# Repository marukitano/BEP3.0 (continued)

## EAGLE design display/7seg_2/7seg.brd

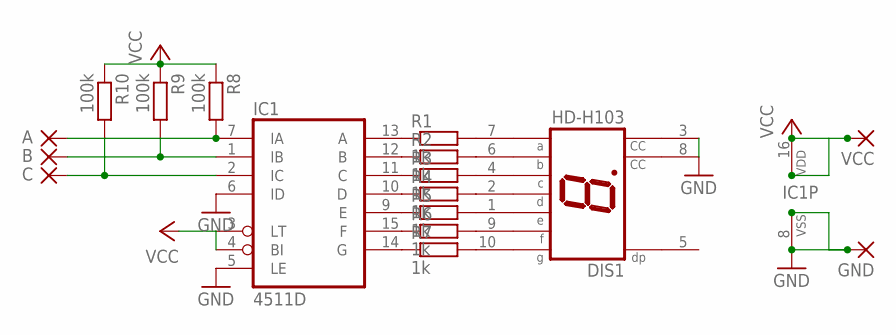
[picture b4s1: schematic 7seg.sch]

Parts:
A: 1,6/0,9
B: 1,6/0,9
C: 1,6/0,9
DIS1: HD-H103; HDSP-M
GND: 1,6/0,9
IC1: 4511D; SO16
R1, R2, R3, R4, R5, R6, R7: 1k; R0805
R8, R9, R10: 100k; R0805
VCC: 1,6/0,9

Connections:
GND: DIS1.3 (CC), DIS1.8 (CC), IC1.5 (LE), IC1.6 (ID), IC1.8 (VSS)
unnamed: IC1.13 (A), R1.1
unnamed: DIS1.7 (A), R1.2
unnamed: IC1.12 (B), R2.1
unnamed: DIS1.6 (B), R2.2
unnamed: IC1.11 (C), R3.1
unnamed: DIS1.4 (C), R3.2
unnamed: IC1.10 (D), R4.1
unnamed: DIS1.2 (D), R4.2
unnamed: IC1.9 (E), R5.1
unnamed: DIS1.1 (E), R5.2
unnamed: IC1.15 (F), R6.1
unnamed: DIS1.9 (F), R6.2
unnamed: IC1.14 (G), R7.1
unnamed: DIS1.10 (G), R7.2
unnamed: A.1, IC1.7 (IA), R8.2
unnamed: B.1, IC1.1 (IB), R9.2
unnamed: C.1, IC1.2 (IC), R10.2
VCC: IC1.3 (LT), IC1.4 (BI), IC1.16 (VDD), R8.1, R9.1, R10.1

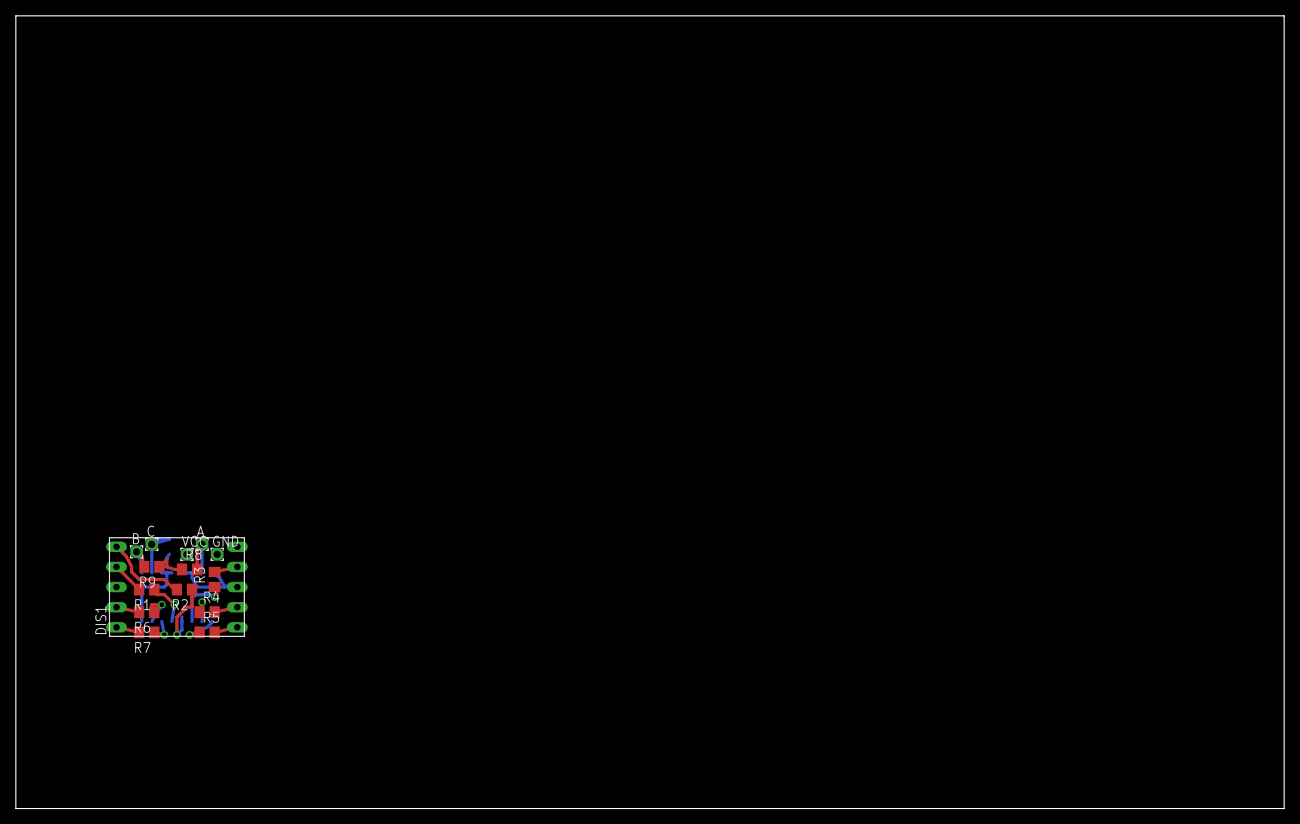
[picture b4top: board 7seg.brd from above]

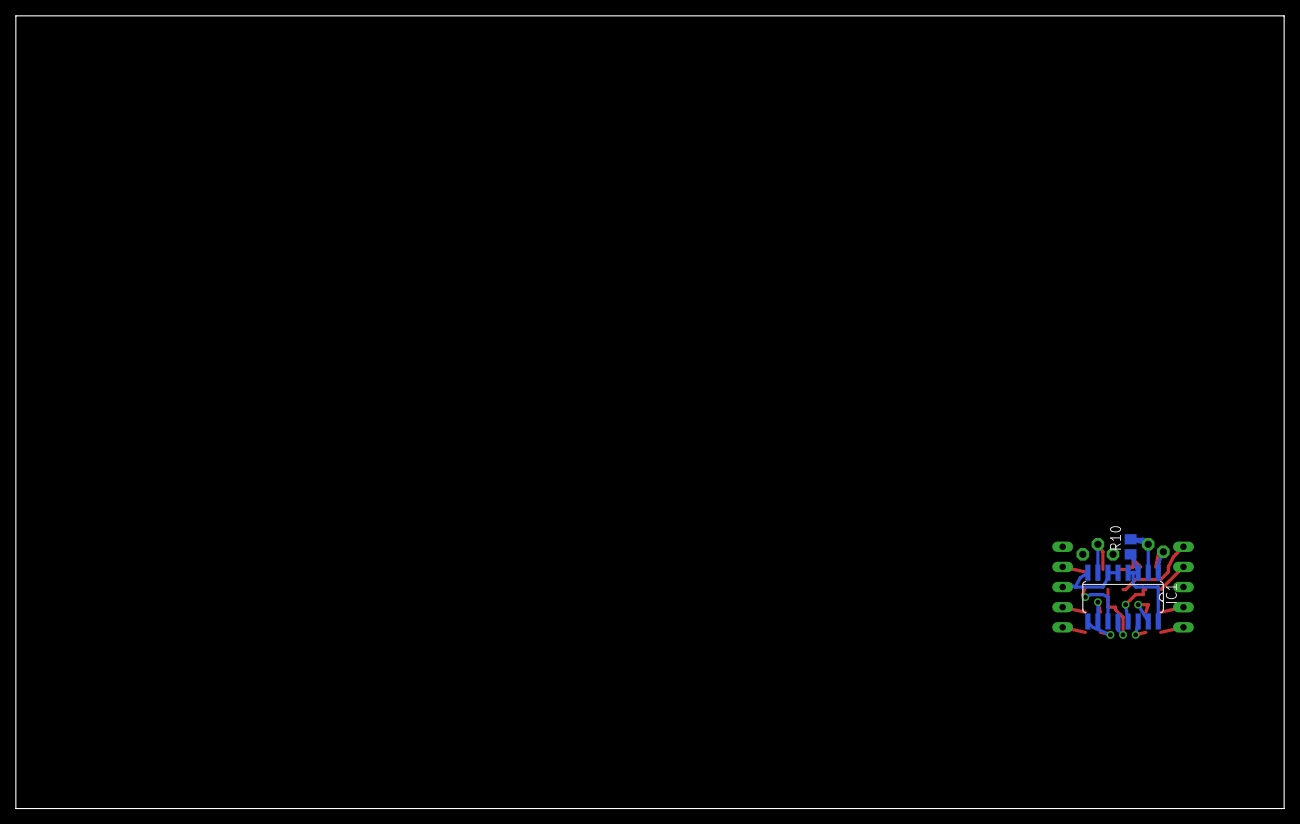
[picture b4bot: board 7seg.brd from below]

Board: 2 copper layers, 160.0 x 100.0 mm, 17 parts (2 on the bottom side), 19 nets.

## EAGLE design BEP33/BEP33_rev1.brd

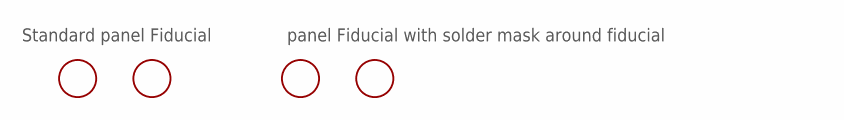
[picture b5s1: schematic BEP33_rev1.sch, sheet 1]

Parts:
FID1, FID2: FIDUCIAL; FIDUCIAL_1MM
FID1B, FID2B: FIDUCIALFIDUCIAL_1MM_WITH_SOLDERMASK; FIDUCIAL_1MM_WITH_SOLDERMASK

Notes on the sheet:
Standard panel Fiducial
panel Fiducial with solder mask around fiducial

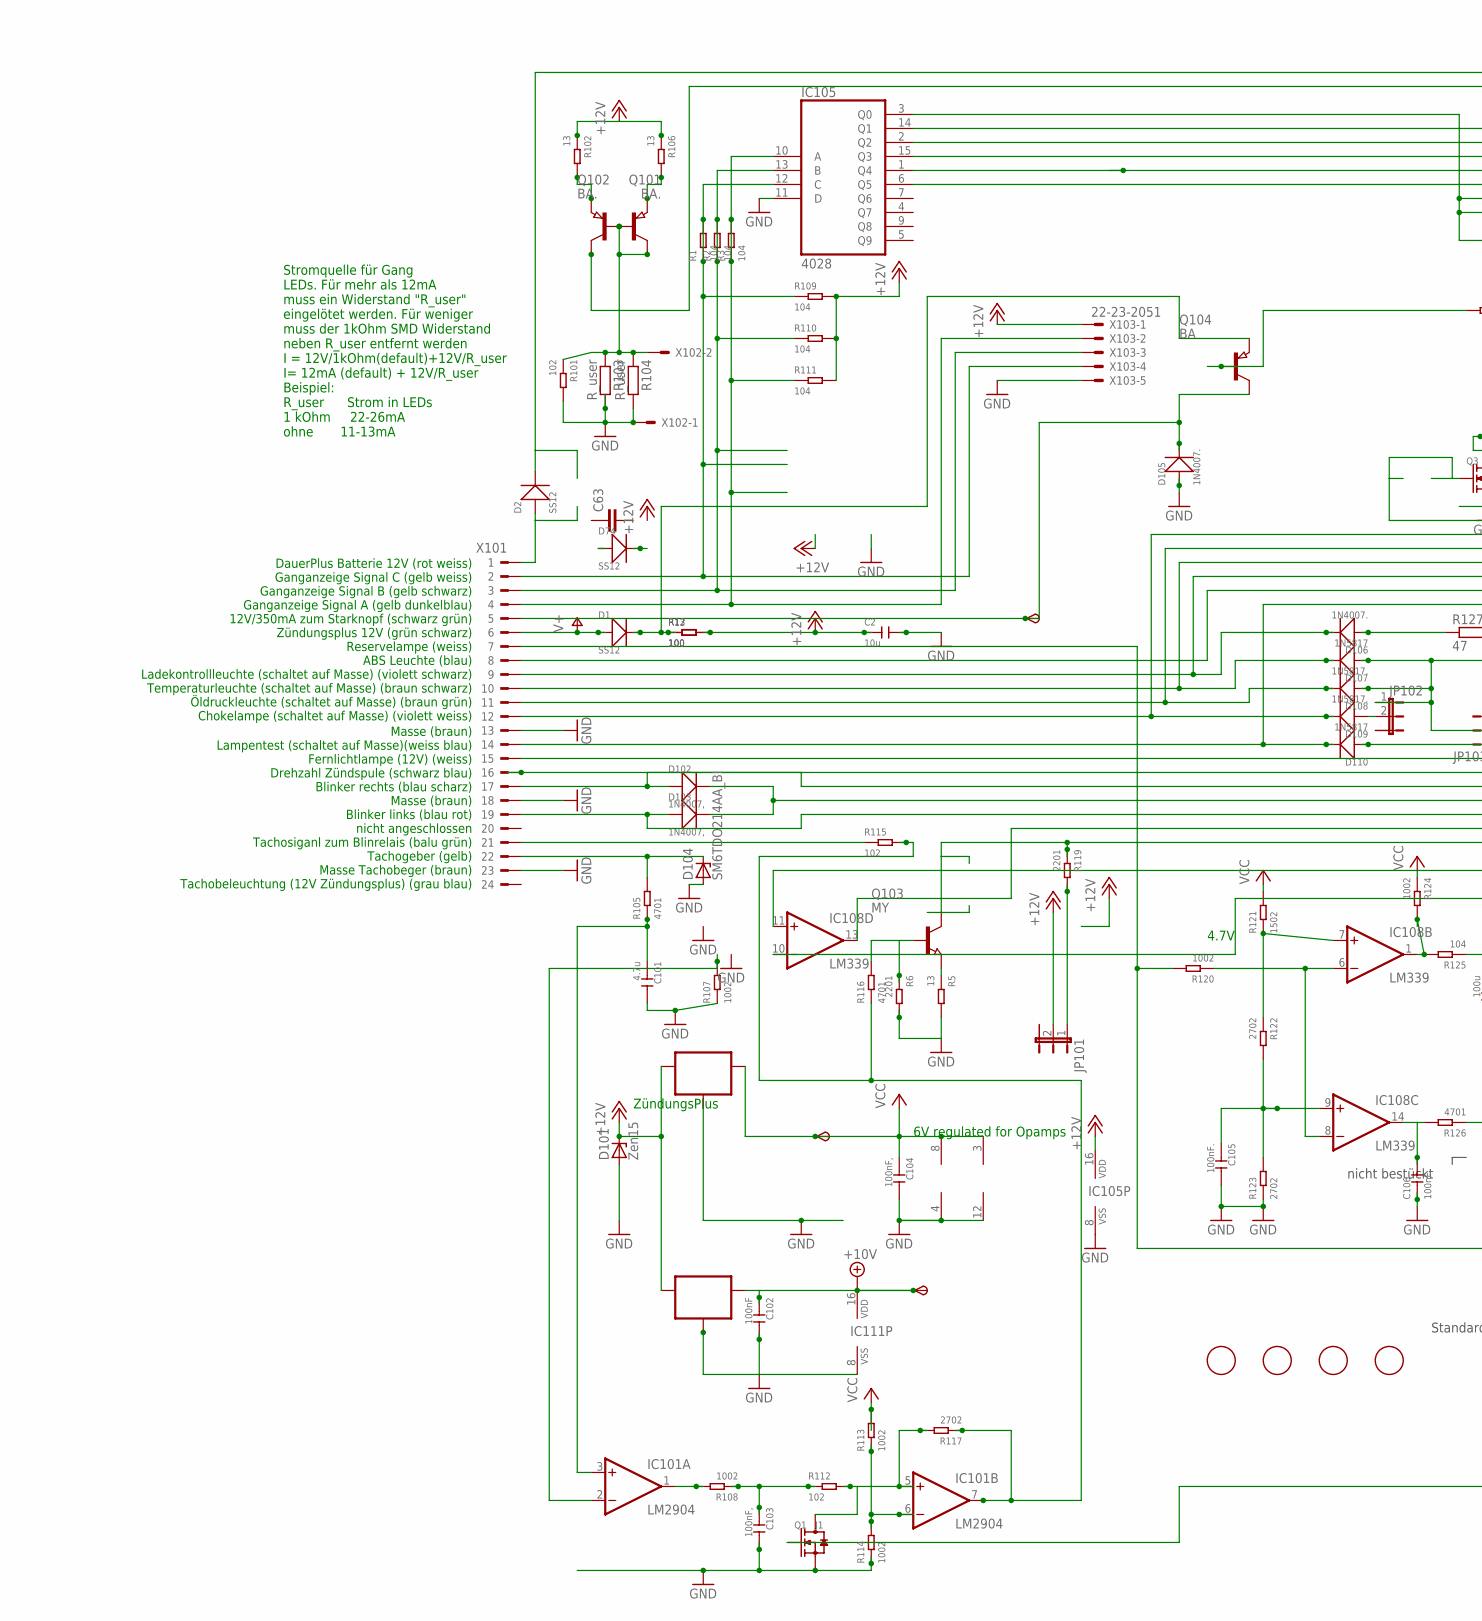
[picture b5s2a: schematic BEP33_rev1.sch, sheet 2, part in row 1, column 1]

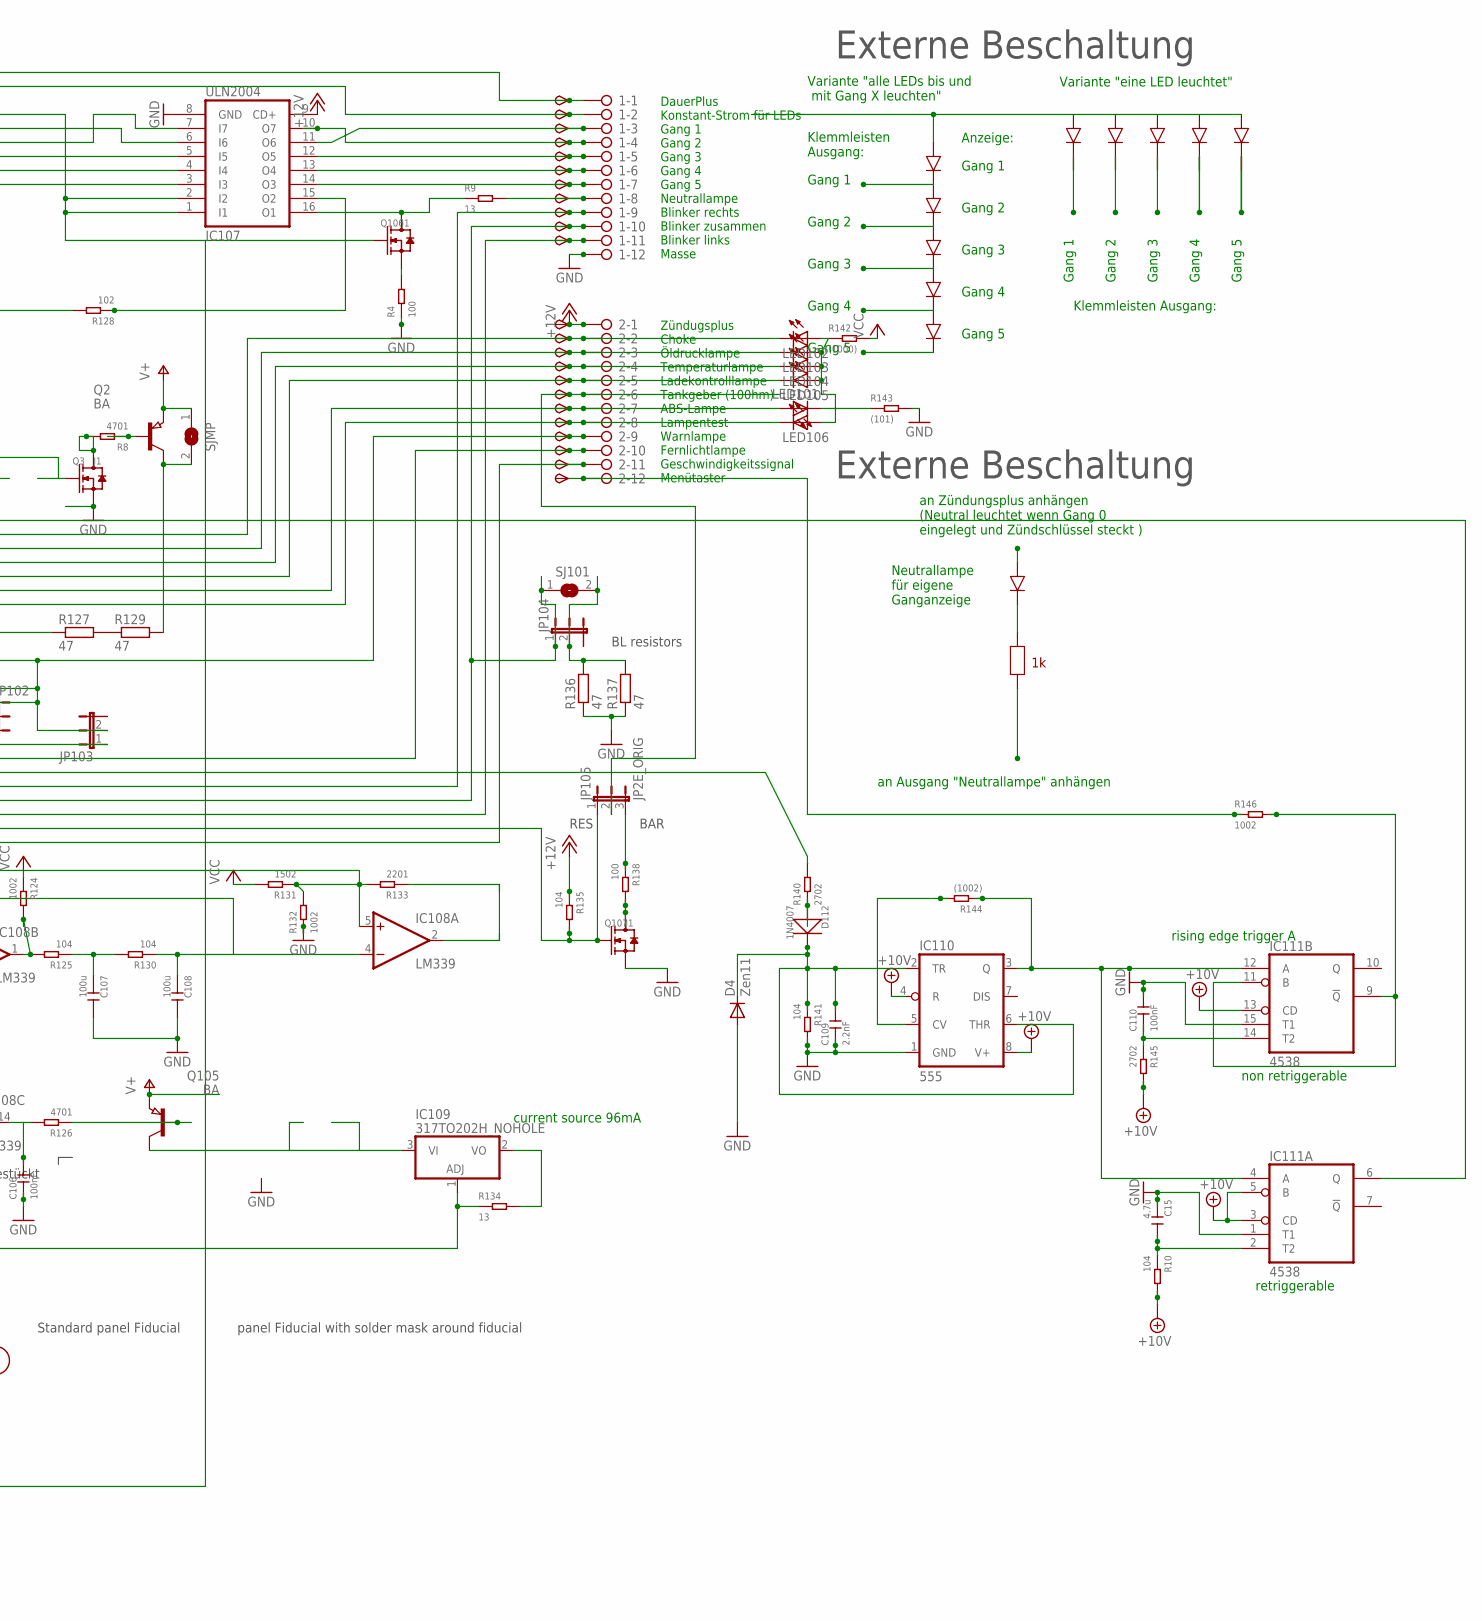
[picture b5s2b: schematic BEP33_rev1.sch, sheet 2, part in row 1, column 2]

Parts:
1, 2: 2081-1132; 12-PIN
6V, 10V: TPSB2.0; B2.0
C2: 10u; C1206
C15, C101: 4.7u; C0805
C63: C-EUC1812K; C1812K
C102, C110: 100nF; C0805
C103, C104: 100nF,; C0805
C105, C106: 100nF.; C0805
C107, C108: 100u; C1206
C109: 2.2nF; C0805
D1, D2, D74: SS12; DO-214AC_SLIM
D4: Zen11; SOD-123_MINI-SMA
D101: Zen15; DO214AA
D102, D103: 1N4007,; DO-214AC
D104: SM6TDO214AA_BI; DO214AA_BI
D105, D106: 1N4007.; DO-214AC
D107, D110: 1N5817; DO-214AC_SLIM
D108, D109: 1N5817.; DO-214AC_SLIM
D112: 1N4007; DO-214AC
FID101, FID102, FID103, FID104: FIDUCIAL; FIDUCIAL_1MM
IC101: LM2904; SO08
IC102: 78L06; SOT89_ROUND
IC104: 78L10; SOT89_ROUND
IC105: 4028; SO16
IC107: ULN2004; SO16
IC108: LM339; SO14
IC109: 317TO202H_NOHOLE; TO220H_NOHOLE
IC110: 555; SO08
IC111: 4538; SO16
JP101, JP102, JP103, JP104: JP2EJP2_SMALLPADS; JP2_SMALLPADS
JP105: JP2E_ORIG; JP2_ORIG_SMALLPADS
LED101, LED102, LED103, LED104, LED105, LED106: LEDLD260; LD260
Q1, Q3, Q106, Q107: J1; SOT-23
Q2, Q104, Q105: BA; SOT89
Q101, Q102: BA.; SOT89
Q103: MY; SOT89
R1, R2, R3, R10, R109, R110, R111, R125, R130, R135, R141: 104; R0805
R4, R12, R13, R138: 100; R0805
R5, R9, R102, R106, R134: 13; R1206
R6, R119, R133: 2201; R0805
R8, R105, R116, R126: 4701; R0805
R101, R112, R115, R128: 102; R0805
R103, R104: R_user; R0805
R107, R108, R113, R114, R120, R124, R132, R146: 1002; R0805
R117, R122, R123, R140, R145: 2702; R0805
R121, R131: 1502; R0805
R127, R129, R136, R137: 47; V235/17_1MM
R142: (1000); R0805
R143: (101); R0805
R144: (1002); R0805
SJ101: SJ
SJMP: SJ
START: TPSB2.0; B2.0
TP1, TP2, TP3, TP4, TP5, TP6, TP7, TP8, TP9, TP10, TP11, TP12, TP13, TP16, TP17, TP18, TP19, TP21, TP22, TP23, TP25, TP26: TPSB2.0; B2.0
TP24: TPSB1,27; B1,27
X101: CON_BMWV2; 24-PIN_V2
X102: 22-23-2021
X103: 22-23-2051

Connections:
+10V: 10V.TP, C102.1, IC104.1 (OUT), IC110.4 (R), IC110.8 (V+), IC111.3 (CD), IC111.5 (B), IC111.13 (CD), IC111.16 (VDD), R10.2, R145.2; also elsewhere on the board
+12V: 2.1, C2.1, D101.C, IC102.3 (IN), IC104.3 (IN), IC105.16 (VDD), IC107.9 (CD+), JP101.2, R12.2, R13.2, R102.1, R106.1, R109.2, R110.2, R111.2, R135.1, TP12.TP, X103.1; also elsewhere on the board
+12V1: 2.11, Q103.2 (C), R119.1, TP26.TP
GND: 1.12, C2.2, C15.1, C101.2, C102.2, C103.2, C104.2, C105.2, C106.1, C107.2, C108.2, C109.1, C110.2, D4.A, D101.A, D104.A, D105.1 (+), IC101.4 (V-), IC102.2 (GND), IC102.2@1 (GND), IC104.2 (GND), IC104.2@1 (GND), IC105.8 (VSS), IC105.11 (D), IC107.8 (GND), IC108.12 (GND), IC110.1 (GND), IC111.1 (T1), IC111.8 (VSS), IC111.15 (T1), Q1.2 (S), Q3.2 (S), Q107.2 (S), R4.1, R5.2, R6.2, R101.2, R103.2, R104.2, R107.1, R114.1, R123.1, R132.1, R136.1, R137.1, R141.2, R143.2, X101.13, X101.18, X101.23, X102.1, X103.5; also elsewhere on the board
unnamed: 2.9, D107.1 (+), D108.1 (+), JP102.1, JP103.2, TP24.TP
unnamed: IC105.10 (A), R3.1, R3.2, R111.1, X101.4, X103.2
unnamed: IC105.13 (B), R2.1, R2.2, R110.1, X101.3, X103.3
unnamed: 2.7, LED101.A, TP22.TP, X101.8
unnamed: Q101.3 (E), R102.2
unnamed: Q2.1 (B), R8.1
unnamed: IC101.2 (-IN), R107.2
unnamed: R127.2, R129.1
unnamed: Q102.3 (E), R106.2
unnamed: D105.2 (-), Q104.2 (C), START.TP, X101.5
unnamed: 2.2, D109.2 (-), LED102.K (C), TP16.TP, X101.12
unnamed: 2.3, D108.2 (-), LED103.K (C), TP17.TP, X101.11
unnamed: 2.4, D107.2 (-), LED104.K (C), TP18.TP, X101.10
unnamed: IC109.3 (VI), Q105.2 (C)
unnamed: IC108.6 (-IN), IC108.8 (-IN), R120.1
unnamed: IC105.12 (C), R1.1, R1.2, R109.1, X101.2, X103.4
unnamed: IC105.15 (Q3), IC107.5 (I5)
unnamed: 2.8, D110.2 (-), LED106.K (C), TP23.TP, X101.14
unnamed: 1.9, D102.1 (+), TP9.TP, X101.17
unnamed: 1.11, D103.1 (+), TP11.TP, X101.19
unnamed: IC111.9 (!Q), IC111.11 (B), R146.2
unnamed: D104.C, R105.2, X101.22
unnamed: C101.1, IC101.3 (+IN), R105.1
unnamed: 1.6, IC107.13 (O4), TP6.TP
unnamed: 1.7, IC107.14 (O3), TP7.TP
unnamed: D1.2 (-), Q104.3 (E), R12.1, R13.1
unnamed: 2.6, JP105.2, TP21.TP
unnamed: JP101.1, R119.2
unnamed: C105.1, IC108.9 (+IN), R122.2, R123.2
unnamed: C106.2, IC108.14 (OUT), R126.2
unnamed: Q3.3 (D), R8.2
unnamed: LED101.K (C), R143.1
unnamed: IC109.1 (ADJ), R120.2, R134.1, X101.7
unnamed: Q105.1 (B), R126.1
unnamed: IC105.2 (Q2), IC107.7 (I7)
unnamed: 1.3, IC107.11 (O6), TP3.TP
unnamed: 1.5, IC107.12 (O5), TP5.TP
unnamed: LED102.A, LED103.A, LED104.A, LED105.A, LED106.A, R142.1
unnamed: R140.2, X101.16
unnamed: Q104.1 (B), R128.2
unnamed: IC105.3 (Q0), IC107.1 (I1), IC107.2 (I2), Q1.1 (G), Q106.1 (G)
unnamed: C107.1, R125.1, R130.2
unnamed: C108.1, IC108.4 (-IN), IC108.10 (-IN), R130.1
unnamed: IC108.5 (+IN), IC108.11 (+IN), R131.1, R132.2, R133.2
unnamed: Q107.3 (D), R138.2
unnamed: IC111.6 (Q), Q3.1 (G)
unnamed: IC105.1 (Q4), IC107.4 (I4)
unnamed: R115.1, X101.21
unnamed: IC107.16 (O1), Q106.3 (D), R9.1
unnamed: 2.10, TP25.TP, X101.15
unnamed: D106.1 (+), R127.1
unnamed: 2.5, D106.2 (-), LED105.K (C), TP19.TP, X101.9
unnamed: IC105.14 (Q1), IC107.6 (I6)
unnamed: Q101.1 (B), Q102.1 (B), Q102.2 (C), R101.1, R103.1, R104.1, X102.2
unnamed: 1.8, R9.2, TP8.TP
unnamed: 1.2, Q101.2 (C), TP2.TP
unnamed: IC108.13 (OUT), JP105.1, Q107.1 (G), R135.2
unnamed: IC105.6 (Q5), IC107.3 (I3)
unnamed: IC109.2 (VO), R134.2
unnamed: IC110.5 (CV), R144.2
unnamed: 1.4, IC107.10 (O7), TP4.TP
unnamed: 1.1, D2.2 (-), TP1.TP
unnamed: IC108.7 (+IN), R121.1, R122.1
unnamed: Q106.2 (S), R4.2
unnamed: Q103.1 (B), R6.1, R116.2
unnamed: IC110.3 (Q), IC111.4 (A), IC111.12 (A), R144.1
unnamed: D112.1 (+), R140.1
unnamed: IC107.15 (O2), R128.1
unnamed: C110.1, IC111.14 (T2), R145.1
unnamed: 2.12, R146.1, TP13.TP
unnamed: D2.1 (+), X101.1
unnamed: IC101.1 (OUT), R108.2
unnamed: 1.10, D102.2 (-), D103.2 (-), JP104.1, SJ101.1, TP10.TP
unnamed: JP104.2, R136.2, R137.2, SJ101.2
unnamed: D109.1 (+), JP102.2
unnamed: C103.1, R108.1, R112.1
unnamed: IC101.5 (+IN), Q1.3 (D), R112.2, R117.2
unnamed: D110.1 (+), JP103.1
unnamed: JP105.3, R138.1
unnamed: Q103.3 (E), R5.1
unnamed: IC101.6 (-IN), R113.1, R114.2
unnamed: C109.2, D4.C, D112.2 (-), IC110.2 (TR), IC110.6 (THR), R141.1
unnamed: C15.2, IC111.2 (T2), R10.1
unnamed: Q2.2 (C), R129.2, SJMP.2
unnamed: IC101.7 (OUT), R115.2, R116.1, R117.1
unnamed: IC108.2 (OUT), R133.1
unnamed: IC108.1 (OUT), R124.2, R125.2
V+: D1.1 (+), Q2.3 (E), Q105.3 (E), SJMP.1, X101.6; also elsewhere on the board
VCC: 6V.TP, C104.1, IC101.8 (V+), IC102.1 (OUT), IC108.3 (V+), R113.2, R121.2, R124.1, R131.2, R142.2; also elsewhere on the board

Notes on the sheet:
6V regulated for Opamps
current source 96mA
ZündungsPlus
Zündugsplus Choke Öldrucklampe Temperaturlampe Ladekontrolllampe Tankgeber (100hm) ABS-Lampe Lampentest Warnlampe Fernlichtlampe Geschwindigkeitssignal Menütaster
DauerPlus Konstant-Strom für LEDs Gang 1 Gang 2 Gang 3 Gang 4 Gang 5 Neutrallampe Blinker rechts Blinker zusammen Blinker links Masse
DauerPlus Batterie 12V (rot weiss) Ganganzeige Signal C (gelb weiss) Ganganzeige Signal B (gelb schwarz) Ganganzeige Signal A (gelb dunkelblau) 12V/350mA zum Starknopf (schwarz grün) Zündungsplus 12V (grün schwarz) Reservelampe (weiss) ABS Leuchte (blau) Ladekontrollleuchte (schaltet auf Masse) (vi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
Masse (braun) Lampentest (schaltet auf Masse)(weiss blau) Fernlichtlampe (12V) (weiss) Drehzahl Zündspule (schwarz blau) Blinker rechts (blau scharz) Masse (braun) Blinker links (blau rot) nicht angeschlossen Tachosiganl zum Blinrelais (balu grün) Tachogeber (gelb) Masse Tachobeger (braun) Tachobel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
4.7V
Stromquelle für Gang LEDs. Für mehr als 12mA muss ein Widerstand "R_user" eingelötet werden. Für weniger muss der 1kOhm SMD Widerstand neben R_user entfernt werden I = 12V/1kOhm(default)+12V/R_user I= 12mA (default) + 12V/R_user Beispiel: R_user Strom in LEDs 1 kOhm 22-26mA ohne 11-13mA
Gang 1
Gang 2
Gang 3
Gang 4
Gang 5
Variante "eine LED leuchtet"
Variante "alle LEDs bis und mit Gang X leuchten"
Klemmleisten Ausgang:
Klemmleisten Ausgang:
an Zündungsplus anhängen (Neutral leuchtet wenn Gang 0 eingelegt und Zündschlüssel steckt )
an Ausgang "Neutrallampe" anhängen
Neutrallampe für eigene Ganganzeige
Externe Beschaltung
Anzeige:
nicht bestückt
rising edge trigger A
BAR
RES
BL resistors
Standard panel Fiducial
panel Fiducial with solder mask around fiducial
non retriggerable
retriggerable

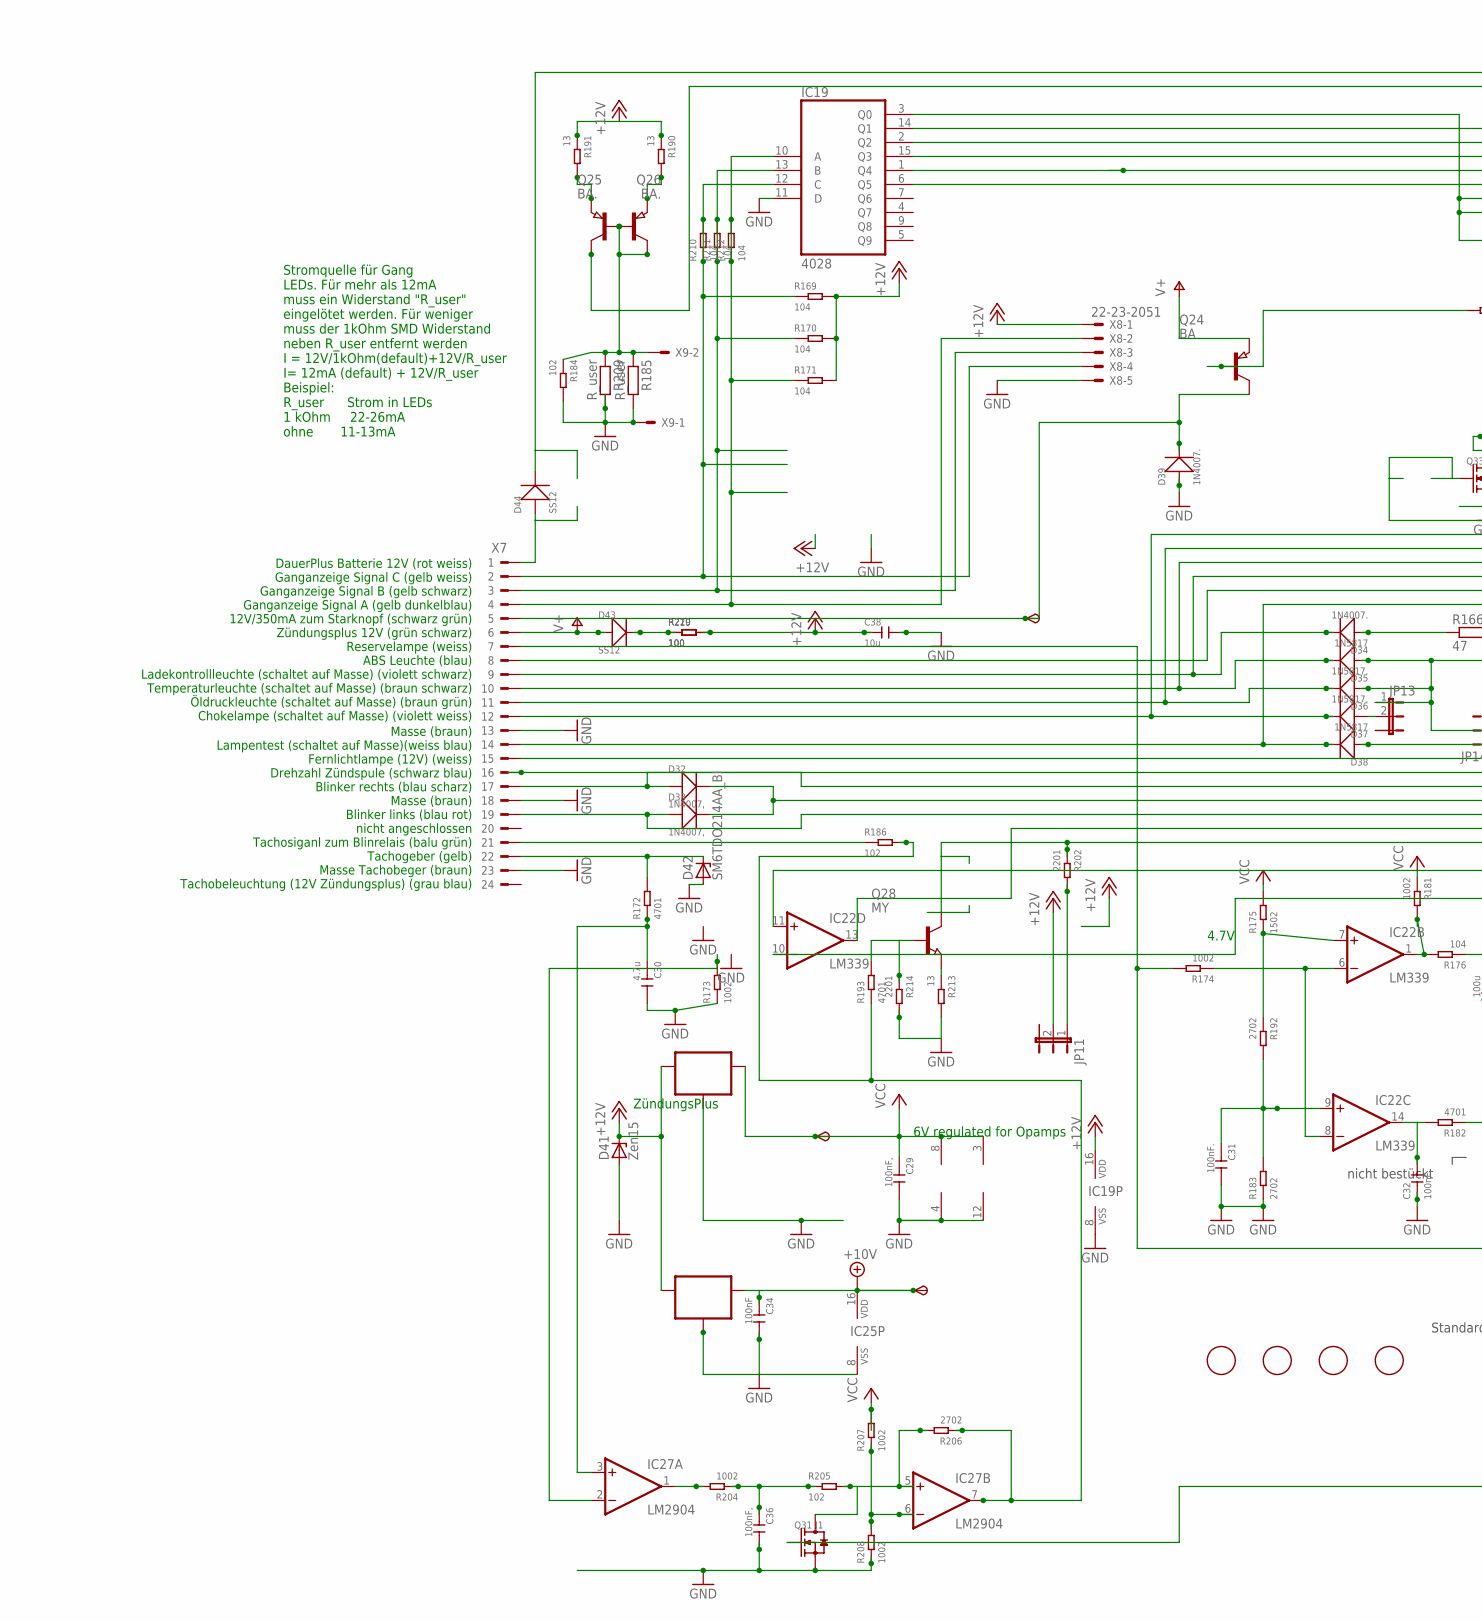
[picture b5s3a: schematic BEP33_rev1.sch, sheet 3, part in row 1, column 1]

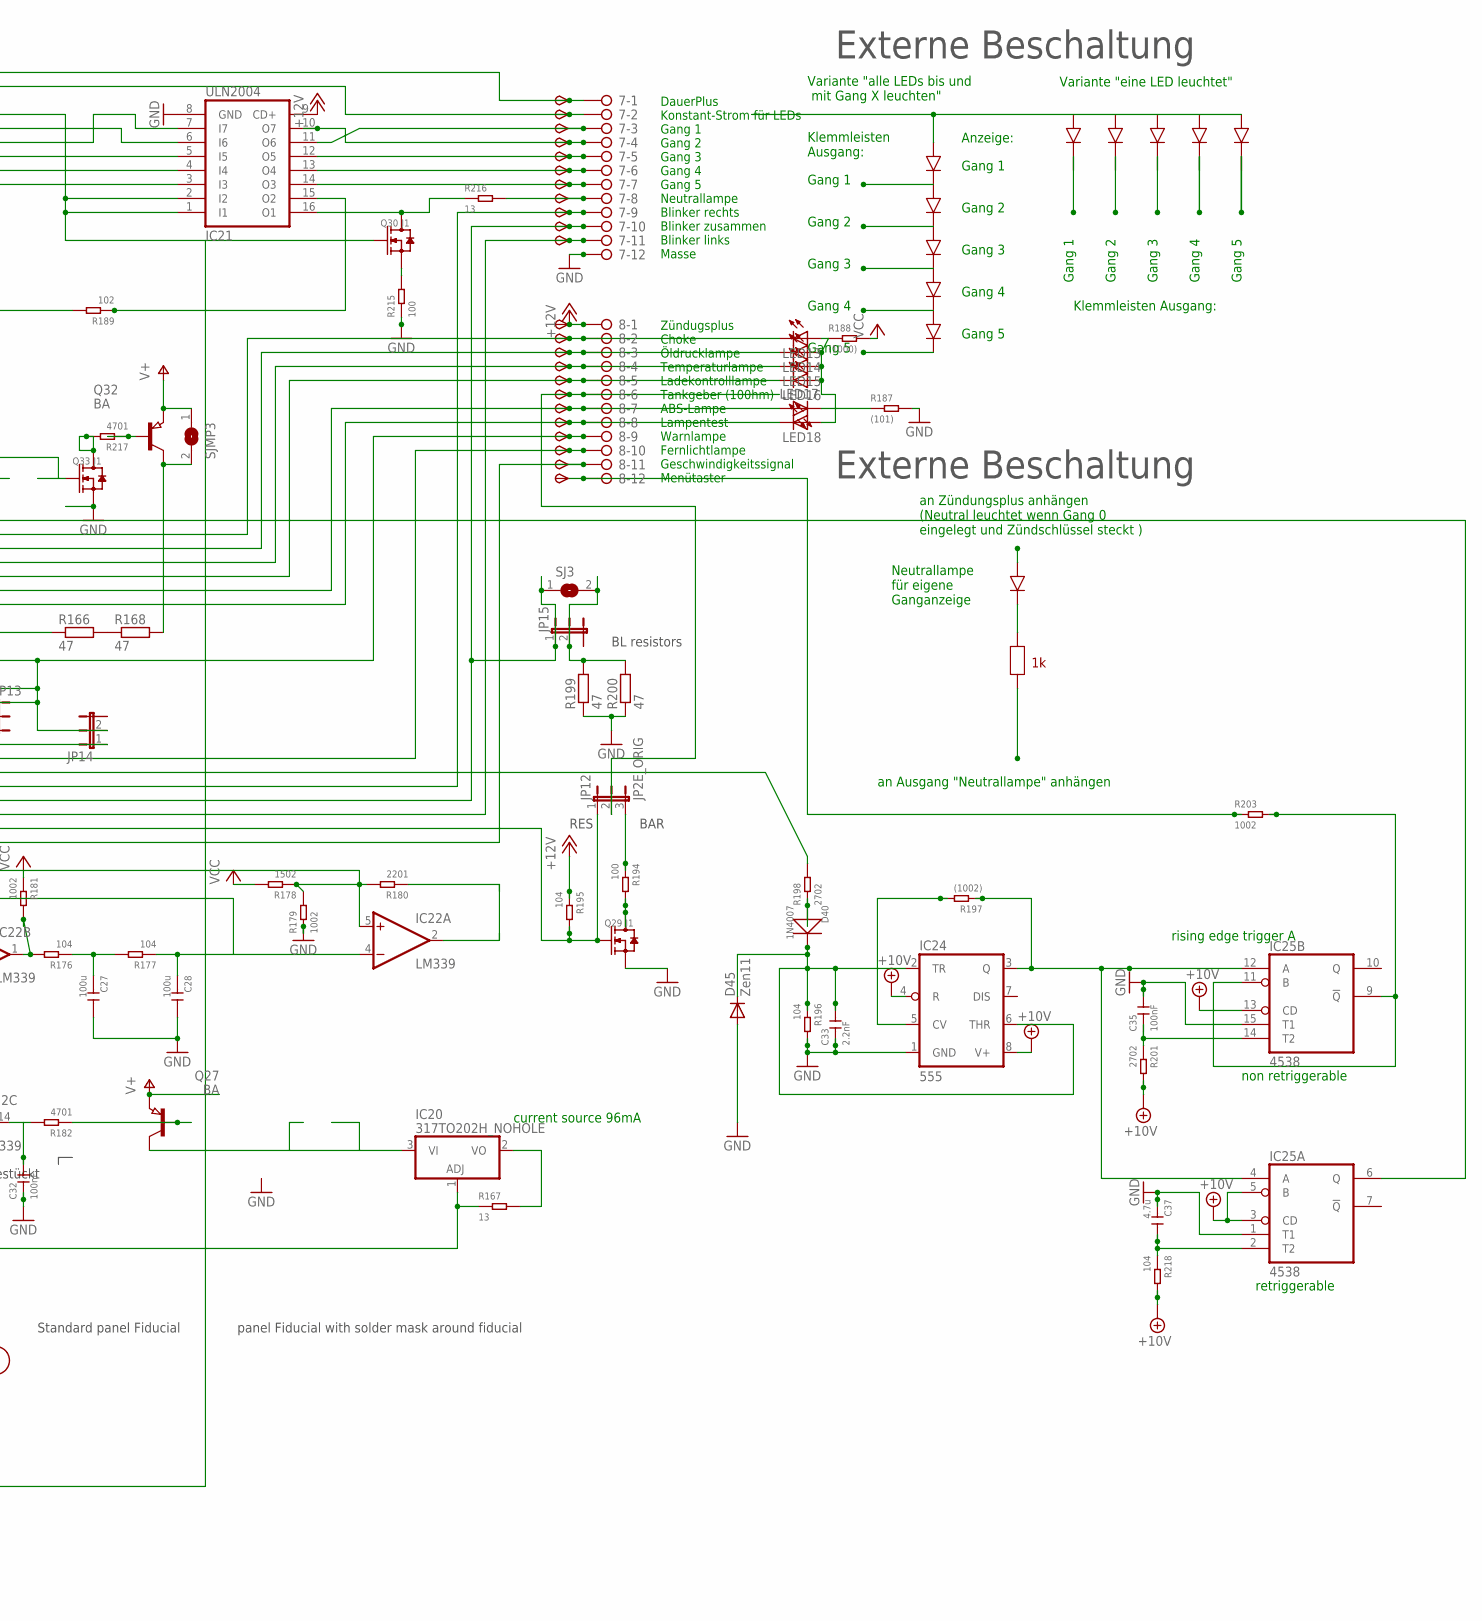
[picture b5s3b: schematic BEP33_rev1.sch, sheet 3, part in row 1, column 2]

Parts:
6V3, 10V3: TPSB2.0; B2.0
7, 8: 2081-1132; 12-PIN
C27, C28: 100u; C1206
C29, C36: 100nF,; C0805
C30, C37: 4.7u; C0805
C31, C32: 100nF.; C0805
C33: 2.2nF; C0805
C34, C35: 100nF; C0805
C38: 10u; C1206
D32, D33: 1N4007,; DO-214AC
D34, D39: 1N4007.; DO-214AC
D35, D38: 1N5817; DO-214AC_SLIM
D36, D37: 1N5817.; DO-214AC_SLIM
D40: 1N4007; DO-214AC
D41: Zen15; DO214AA
D42: SM6TDO214AA_BI; DO214AA_BI
D43, D44: SS12; DO-214AC_SLIM
D45: Zen11; SOD-123_MINI-SMA
FID11, FID12, FID13, FID14: FIDUCIAL; FIDUCIAL_1MM
IC19: 4028; SO16
IC20: 317TO202H_NOHOLE; TO220H_NOHOLE
IC21: ULN2004; SO16
IC22: LM339; SO14
IC23: 78L06; SOT89_ROUND
IC24: 555; SO08
IC25: 4538; SO16
IC26: 78L10; SOT89_ROUND
IC27: LM2904; SO08
JP11, JP13, JP14, JP15: JP2EJP2_SMALLPADS; JP2_SMALLPADS
JP12: JP2E_ORIG; JP2_ORIG_SMALLPADS
LED13, LED14, LED15, LED16, LED17, LED18: LEDLD260; LD260
Q24, Q27, Q32: BA; SOT89
Q25, Q26: BA.; SOT89
Q28: MY; SOT89
Q29, Q30, Q31, Q33: J1; SOT-23
R166, R168, R199, R200: 47; V235/17_1MM
R167, R190, R191, R213, R216: 13; R1206
R169, R170, R171, R176, R177, R195, R196, R210, R211, R212, R218: 104; R0805
R172, R182, R193, R217: 4701; R0805
R173, R174, R179, R181, R203, R204, R207, R208: 1002; R0805
R175, R178: 1502; R0805
R180, R202, R214: 2201; R0805
R183, R192, R198, R201, R206: 2702; R0805
R184, R186, R189, R205: 102; R0805
R185, R209: R_user; R0805
R187: (101); R0805
R188: (1000); R0805
R194, R215, R219, R220: 100; R0805
R197: (1002); R0805
SJ3: SJ
SJMP3: SJ
START3: TPSB2.0; B2.0
TP70, TP71, TP72, TP73, TP74, TP75, TP76, TP77, TP78, TP79, TP80, TP81, TP82, TP83, TP84, TP85, TP86, TP87, TP89, TP90, TP91, TP92: TPSB2.0; B2.0
TP88: TPSB1,27; B1,27
X7: CON_BMWV2; 24-PIN_V2
X8: 22-23-2051
X9: 22-23-2021

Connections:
+10V: 10V3.TP, C34.1, IC24.4 (R), IC24.8 (V+), IC25.3 (CD), IC25.5 (B), IC25.13 (CD), IC25.16 (VDD), IC26.1 (OUT), R201.2, R218.2; also elsewhere on the board
+12V: 8.1, C38.1, D41.C, IC19.16 (VDD), IC21.9 (CD+), IC23.3 (IN), IC26.3 (IN), JP11.2, R169.2, R170.2, R171.2, R190.1, R191.1, R195.1, R219.2, R220.2, TP91.TP, X8.1; also elsewhere on the board
+12V4: 8.11, Q28.2 (C), R202.1, TP90.TP
GND: 7.12, C27.2, C28.2, C29.2, C30.2, C31.2, C32.1, C33.1, C34.2, C35.2, C36.2, C37.1, C38.2, D39.1 (+), D41.A, D42.A, D45.A, IC19.8 (VSS), IC19.11 (D), IC21.8 (GND), IC22.12 (GND), IC23.2 (GND), IC23.2@1 (GND), IC24.1 (GND), IC25.1 (T1), IC25.8 (VSS), IC25.15 (T1), IC26.2 (GND), IC26.2@1 (GND), IC27.4 (V-), Q29.2 (S), Q31.2 (S), Q33.2 (S), R173.1, R179.1, R183.1, R184.2, R185.2, R187.2, R196.2, R199.1, R200.1, R208.1, R209.2, R213.2, R214.2, R215.1, X7.13, X7.18, X7.23, X8.5, X9.1; also elsewhere on the board
unnamed: R166.2, R168.1
unnamed: 8.9, D35.1 (+), D36.1 (+), JP13.1, JP14.2, TP88.TP
unnamed: IC19.10 (A), R171.1, R212.1, R212.2, X7.4, X8.2
unnamed: IC19.13 (B), R170.1, R211.1, R211.2, X7.3, X8.3
unnamed: D39.2 (-), Q24.2 (C), START3.TP, X7.5
unnamed: IC19.12 (C), R169.1, R210.1, R210.2, X7.2, X8.4
unnamed: 8.7, LED17.A, TP86.TP, X7.8
unnamed: 8.2, D37.2 (-), LED13.K (C), TP81.TP, X7.12
unnamed: 8.3, D36.2 (-), LED14.K (C), TP82.TP, X7.11
unnamed: 8.4, D35.2 (-), LED15.K (C), TP83.TP, X7.10
unnamed: 8.8, D38.2 (-), LED18.K (C), TP87.TP, X7.14
unnamed: 7.9, D32.1 (+), TP78.TP, X7.17
unnamed: 7.11, D33.1 (+), TP80.TP, X7.19
unnamed: D42.C, R172.2, X7.22
unnamed: C30.1, IC27.3 (+IN), R172.1
unnamed: IC22.1 (OUT), R176.2, R181.2
unnamed: C27.1, R176.1, R177.2
unnamed: C28.1, IC22.4 (-IN), IC22.10 (-IN), R177.1
unnamed: IC22.5 (+IN), IC22.11 (+IN), R178.1, R179.2, R180.2
unnamed: C31.1, IC22.9 (+IN), R183.2, R192.2
unnamed: C32.2, IC22.14 (OUT), R182.2
unnamed: Q27.1 (B), R182.1
unnamed: IC19.2 (Q2), IC21.7 (I7)
unnamed: 7.5, IC21.12 (O5), TP74.TP
unnamed: IC19.1 (Q4), IC21.4 (I4)
unnamed: 8.10, TP89.TP, X7.15
unnamed: 8.5, D34.2 (-), LED16.K (C), TP84.TP, X7.9
unnamed: D34.1 (+), R166.1
unnamed: IC19.6 (Q5), IC21.3 (I3)
unnamed: 7.4, IC21.10 (O7), TP73.TP
unnamed: IC20.1 (ADJ), R167.1, R174.2, X7.7
unnamed: IC22.6 (-IN), IC22.8 (-IN), R174.1
unnamed: 7.2, Q26.2 (C), TP71.TP
unnamed: 7.1, D44.2 (-), TP70.TP
unnamed: R198.2, X7.16
unnamed: IC19.15 (Q3), IC21.5 (I5)
unnamed: 7.6, IC21.13 (O4), TP75.TP
unnamed: 7.7, IC21.14 (O3), TP76.TP
unnamed: 8.6, JP12.2, TP85.TP
unnamed: LED17.K (C), R187.1
unnamed: LED13.A, LED14.A, LED15.A, LED16.A, LED18.A, R188.1
unnamed: Q24.1 (B), R189.2
unnamed: IC19.3 (Q0), IC21.1 (I1), IC21.2 (I2), Q30.1 (G), Q31.1 (G)
unnamed: IC19.14 (Q1), IC21.6 (I6)
unnamed: 7.3, IC21.11 (O6), TP72.TP
unnamed: Q25.1 (B), Q25.2 (C), Q26.1 (B), R184.1, R185.1, R209.1, X9.2
unnamed: Q26.3 (E), R191.2
unnamed: Q25.3 (E), R190.2
unnamed: IC22.7 (+IN), R175.1, R192.1
unnamed: IC27.2 (-IN), R173.2
unnamed: Q28.1 (B), R193.2, R214.1
unnamed: Q29.3 (D), R194.2
unnamed: IC20.2 (VO), R167.2
unnamed: IC20.3 (VI), Q27.2 (C)
unnamed: IC24.5 (CV), R197.2
unnamed: IC24.3 (Q), IC25.4 (A), IC25.12 (A), R197.1
unnamed: D40.1 (+), R198.1
unnamed: 7.10, D32.2 (-), D33.2 (-), JP15.1, SJ3.1, TP79.TP
unnamed: JP15.2, R199.2, R200.2, SJ3.2
unnamed: IC25.9 (!Q), IC25.11 (B), R203.2
unnamed: C35.1, IC25.14 (T2), R201.1
unnamed: JP11.1, R202.2
unnamed: IC21.15 (O2), R189.1
unnamed: 8.12, R203.1, TP92.TP
unnamed: D37.1 (+), JP13.2
unnamed: IC27.1 (OUT), R204.2
unnamed: C36.1, R204.1, R205.1
unnamed: IC27.5 (+IN), Q31.3 (D), R205.2, R206.2
unnamed: IC27.6 (-IN), R207.1, R208.2
unnamed: D38.1 (+), JP14.1
unnamed: JP12.3, R194.1
unnamed: IC22.13 (OUT), JP12.1, Q29.1 (G), R195.2
unnamed: R186.1, X7.21
unnamed: IC21.16 (O1), Q30.3 (D), R216.1
unnamed: D43.2 (-), R219.1, R220.1
unnamed: 7.8, R216.2, TP77.TP
unnamed: Q30.2 (S), R215.2
unnamed: D44.1 (+), X7.1
unnamed: Q28.3 (E), R213.1
unnamed: C33.2, D40.2 (-), D45.C, IC24.2 (TR), IC24.6 (THR), R196.1
unnamed: Q32.1 (B), R217.1
unnamed: Q33.3 (D), R217.2
unnamed: Q32.2 (C), R168.2, SJMP3.2
unnamed: IC27.7 (OUT), R186.2, R193.1, R206.1
unnamed: IC22.2 (OUT), R180.1
unnamed: IC25.6 (Q), Q33.1 (G)
unnamed: C37.2, IC25.2 (T2), R218.1
V+: D43.1 (+), Q24.3 (E), Q27.3 (E), Q32.3 (E), SJMP3.1, X7.6; also elsewhere on the board
VCC: 6V3.TP, C29.1, IC22.3 (V+), IC23.1 (OUT), IC27.8 (V+), R175.2, R178.2, R181.1, R188.2, R207.2; also elsewhere on the board

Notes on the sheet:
6V regulated for Opamps
current source 96mA
ZündungsPlus
Zündugsplus Choke Öldrucklampe Temperaturlampe Ladekontrolllampe Tankgeber (100hm) ABS-Lampe Lampentest Warnlampe Fernlichtlampe Geschwindigkeitssignal Menütaster
DauerPlus Konstant-Strom für LEDs Gang 1 Gang 2 Gang 3 Gang 4 Gang 5 Neutrallampe Blinker rechts Blinker zusammen Blinker links Masse
DauerPlus Batterie 12V (rot weiss) Ganganzeige Signal C (gelb weiss) Ganganzeige Signal B (gelb schwarz) Ganganzeige Signal A (gelb dunkelblau) 12V/350mA zum Starknopf (schwarz grün) Zündungsplus 12V (grün schwarz) Reservelampe (weiss) ABS Leuchte (blau) Ladekontrollleuchte (schaltet auf Masse) (vi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
Masse (braun) Lampentest (schaltet auf Masse)(weiss blau) Fernlichtlampe (12V) (weiss) Drehzahl Zündspule (schwarz blau) Blinker rechts (blau scharz) Masse (braun) Blinker links (blau rot) nicht angeschlossen Tachosiganl zum Blinrelais (balu grün) Tachogeber (gelb) Masse Tachobeger (braun) Tachobel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
4.7V
Stromquelle für Gang LEDs. Für mehr als 12mA muss ein Widerstand "R_user" eingelötet werden. Für weniger muss der 1kOhm SMD Widerstand neben R_user entfernt werden I = 12V/1kOhm(default)+12V/R_user I= 12mA (default) + 12V/R_user Beispiel: R_user Strom in LEDs 1 kOhm 22-26mA ohne 11-13mA
Gang 1
Gang 2
Gang 3
Gang 4
Gang 5
Variante "eine LED leuchtet"
Variante "alle LEDs bis und mit Gang X leuchten"
Klemmleisten Ausgang:
Klemmleisten Ausgang:
an Zündungsplus anhängen (Neutral leuchtet wenn Gang 0 eingelegt und Zündschlüssel steckt )
an Ausgang "Neutrallampe" anhängen
Neutrallampe für eigene Ganganzeige
Externe Beschaltung
Anzeige:
nicht bestückt
rising edge trigger A
BAR
RES
BL resistors
Standard panel Fiducial
panel Fiducial with solder mask around fiducial
non retriggerable
retriggerable
